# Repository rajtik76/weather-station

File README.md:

# Balcony Station

A weather station on an east-facing balcony in Plzeň, Czech Republic,
measuring temperature, humidity and pressure. Its goal is to estimate
outdoor air temperature as accurately as possible by correcting the
heating error of this particular radiation shield and balcony setup.

The SHT4x measures temperature inside a passive radiation shield. Sunlight
can heat the shield and make the sensor read above the surrounding air
temperature. The project aims to retain the original readings and show a
corrected estimate alongside them.

**Current status:** a PHP correction model can be calibrated and evaluated
against ČHMÚ observations through Artisan. Overview and Charts display
the original temperature alongside the calculated shade estimate. The
Reference page compares the shade estimate with the shade reference and
Mikulka by day, up to 30 days back, and reports deviations over the last
30 days.

Running at [weather.rajtik.com](https://weather.rajtik.com).

## Reference and evaluation

ČHMÚ Plzeň-Mikulka, approximately 3.5 km away, is the professional reference
for developing and evaluating the correction. Its historical observations
are available through [ČHMÚ open data](https://opendata.chmi.cz/meteorology/climate/).
Location, elevation and microclimate can produce real differences between
Mikulka and the balcony; agreement with Mikulka is a measurable reference,
with that limitation.

The correction is therefore fitted and judged against a shade reference
(`ShadeReference`): Mikulka shifted by the balcony's own offset from it.
The offset is read while the shield is in shade, in the hour before the
sun reaches it (below 300 lx) and 30 to 60 minutes after the sun has left,
and runs in a straight line between the two from the moment the sun
reaches the shield until an hour after it leaves, while the shield's
heating history decays. Outside that window the shade reference is
Mikulka. A day without both anchors has no reference in that window, and
its readings there are left out of calibration and validation. On overcast mornings between 1 October
and 5 November 2026, when the right difference is zero, the shade reference
was 0.21 °C from zero on average and Mikulka 0.52 °C. The straight line
between the anchors is an assumption that overcast mornings cannot check.

The correction will be evaluated against the uncorrected sensor on the
same observations, using days excluded from calibration. Both the mean
absolute error and the mean signed error should be compared, with sunny
periods and nights evaluated separately.

The setup changed during the record:

- Radiation shield installed on **16 September 2026 at 15:00 Europe/Prague**
- BME280 replaced by an SHT4x on 23 September 2026
- SHT4x sensor replaced and VEML7700 installed on 30 September 2026

These events are recorded in `station_events` and marked on the charts.
They do not block calibration or invalidate an existing correction model.

## Temperature correction

The model estimates solar heating from light inside the shield and the
Sun's position relative to the balcony wall. Feature version 2 combines
the current light with exponentially weighted histories of 10 and 30
minutes, and scales the 10 minute history by low sun (below 20° elevation
the shield heats more for the same light) and by the microphone's 25 Hz
band (wind ventilates the shield). Regularized regression learns the
response of this installation; heating coefficients stay non-negative, the
wind term takes either sign. Version 1 (light with 20 and 60 minute histories)
is still applied for calibrations trained with it. The shade estimate is
the measured temperature minus the estimated heating; original records
are unchanged.

Calibration and inference run in PHP, without a separate service. ČHMÚ
temperature is used for calibration and evaluation only. The running model
uses the station's light and sound history, time and calibrated
installation geometry.
The wall direction is the balcony facade at 71.8° clockwise from true north;
override it when calibrating another installation.

```sh
php artisan temperature:import-reference
php artisan temperature:import-reference --days=30
php artisan temperature:import-reference --month=2026-09
php artisan temperature:import-reference /path/to/mikulka-20261001.json
php artisan temperature:calibrate sensor-001 --from=2026-09-30 --validate-from=2026-10-10 --until=2026-10-15
php artisan temperature:show sensor-001
```

Dates are local calendar boundaries in Europe/Prague, with exclusive ends.
Station events do not restrict the calibration range. At least
seven calibration days and three later validation days must each have
100 reference pairs; calibration also needs two sunlit mornings. Validation
reports MAE and signed error for the same raw and corrected observations,
split into sun-facing periods, daytime shade and night, plus each day.
The validation days are never used to fit coefficients. An accepted model
is available to inference only after its validation period ends.

The scheduler imports the previous and current UTC day's references every
hour. Run `--days=30` once to backfill history from monthly and daily
archives; the scheduled import continues to fetch only yesterday and today. Missing reference periods stay missing. ČHMÚ's good
and unknown-quality observations are eligible; suspect, poor, estimated,
missing and flagged observations are excluded.

The model needs an uninterrupted hour of light measurements after startup
or a gap. Unsupported readings and inputs beyond its calibrated light or
heating range return no estimate. Validation scores against the shade
reference. With at least two sunlit validation mornings, acceptance
requires a sun-facing MAE at least 10% below the raw sensor and a smaller
sun-facing bias; with fewer, the sun-facing MAE may not exceed the raw
sensor's by more than 0.05 °C. Always: no overall MAE increase above
0.05 °C, at least 90% validation coverage, no MAE increase above 0.05 °C at
night or 0.1 °C in daytime shade. A retrained model must also be within
0.02 °C of the model in use, overall and sun-facing, on the same pairs.

The model corrects solar heating. Local air differences, reflected heat
from the building and night-time radiation are not corrected: in afternoon
shade the balcony runs up to about a degree colder than Mikulka on sunny,
calm days and warmer on windy, overcast ones, and that is the balcony's
air, not the shield. A smaller error against the shade reference is
evidence of a better shield correction, not a measurement of the remaining
error on the balcony. Calibration over a few autumn days
does not establish accuracy in other seasons.

## Measurements

```text
SHT4x    --I2C--+
VEML7700 --I2C--+
BMP280   --I2C--+--> ESP32 --HTTPS--> Laravel API --> PostgreSQL
INMP441  --I2S--+                                      |
                                                 Livewire pages
```

- SHT4x: temperature and humidity, outside in the radiation shield
- BMP280: pressure, on the indoor base board; its temperature is unused
- VEML7700: light inside the shield, retained as a potential correction input
- INMP441: sound in the shield, with an experimental indication of rain from its spectrum
- Samples every 30 seconds, uploaded as ten-minute windows with means and extremes
- Original measurements remain stored in the firmware's units; display conversions happen on read

Light behind the shield's louvers is specific to this mounting. Its absolute
lux values are not an open-sky radiation measurement. The microphone's rain
indication is experimental: its thresholds were fitted to this mounting
against ČHMÚ Mikulka's rain gauge, and the owner's reports on Discord keep
checking it.

## Run it

Requires PHP 8.4, Node 24 and Docker. Docker Compose runs PostgreSQL 18;
Laravel Herd serves the local site and Vite provides the development assets.

```sh
docker compose up -d
composer setup
npm run dev
```

For a local demonstration, `php artisan migrate:fresh --seed` replaces the
local database with a month of sample measurements for two stations. The
sample weather series comes from ČHMÚ Plzeň-Mikulka, with synthetic station
variation, light and sound added for the dashboard.

ČHMÚ data is licensed CC BY 4.0. Source: Czech Hydrometeorological Institute.
The sample series uses hourly means of its ten-minute observations for
August 2025. Sample pressure is adjusted from Mikulka's elevation of 359.8 m
to the balcony's 345 m before the synthetic station variation is added.

## Documentation

- [`docs/development.md`](docs/development.md): application structure, configuration, checks and deployment
- [`docs/api.md`](docs/api.md): ingest protocol and storage
- [`firmware/README.md`](firmware/README.md): wiring, protocol and hardware notes
- [`firmware/CHANGELOG.md`](firmware/CHANGELOG.md): firmware history
- `docs/hardware/kicad/`: station, shield hub and base board KiCad projects

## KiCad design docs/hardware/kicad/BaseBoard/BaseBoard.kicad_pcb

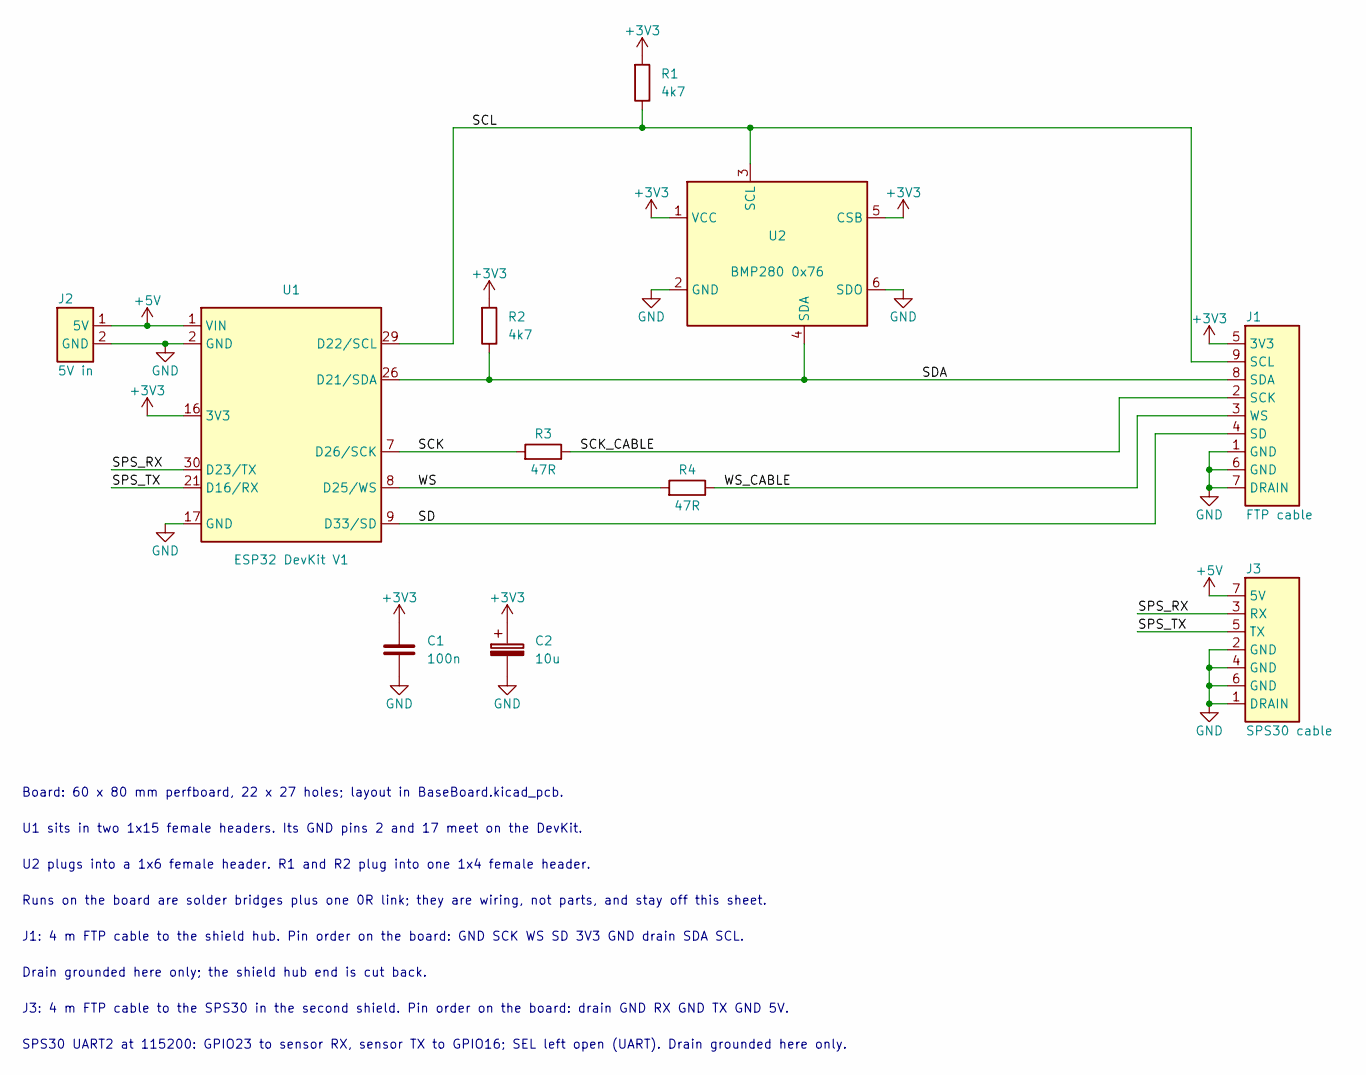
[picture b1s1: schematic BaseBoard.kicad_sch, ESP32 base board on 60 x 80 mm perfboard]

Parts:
C1: 100n; C_Disc_P2.54
C2: 10u; CP_Radial_D5.0mm_P2.54
J1: FTP cable; PinHeader_1x09
J2: 5V in; PinHeader_1x02
J3: SPS30 cable; PinHeader_1x07
R1, R2: 4k7; R_Socketed_1x02
R3, R4: 47R; R_Axial_P10.16
U1: ESP32 DevKit V1; DOIT_ESP32_DevKit_V1_Socketed
U2: BMP280 0x76; BMP280_Module_Socketed

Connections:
+3V3: C1.1, C2.1 (+), J1.5 (3V3), R1.1, R2.1, U1.16 (3V3), U2.1 (VCC), U2.5 (CSB); also elsewhere on the board
+5V: J2.1 (5V), J3.7 (5V), U1.1 (VIN)
/SCK: R3.1, U1.7 (D26/SCK)
/SCK_CABLE: J1.2 (SCK), R3.2
/SCL: J1.9 (SCL), R1.2, U1.29 (D22/SCL), U2.3 (SCL)
/SD: J1.4 (SD), U1.9 (D33/SD)
/SDA: J1.8 (SDA), R2.2, U1.26 (D21/SDA), U2.4 (SDA)
/SPS_RX: J3.3 (RX), U1.30 (D23/TX)
/SPS_TX: J3.5 (TX), U1.21 (D16/RX)
/WS: R4.1, U1.8 (D25/WS)
/WS_CABLE: J1.3 (WS), R4.2
GND: C1.2, C2.2 (-), J1.1 (GND), J1.6 (GND), J1.7 (DRAIN), J2.2 (GND), J3.1 (DRAIN), J3.2 (GND), J3.4 (GND), J3.6 (GND), U1.2 (GND), U1.17 (GND), U2.2 (GND), U2.6 (SDO)

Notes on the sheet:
Board: 60 x 80 mm perfboard, 22 x 27 holes; layout in BaseBoard.kicad_pcb.
U1 sits in two 1x15 female headers. Its GND pins 2 and 17 meet on the DevKit.
U2 plugs into a 1x6 female header. R1 and R2 plug into one 1x4 female header.
Runs on the board are solder bridges plus one 0R link; they are wiring, not parts, and stay off this sheet.
J1: 4 m FTP cable to the shield hub. Pin order on the board: GND SCK WS SD 3V3 GND drain SDA SCL.
Drain grounded here only; the shield hub end is cut back.
J3: 4 m FTP cable to the SPS30 in the second shield. Pin order on the board: drain GND RX GND TX GND 5V.
SPS30 UART2 at 115200: GPIO23 to sensor RX, sensor TX to GPIO16; SEL left open (UART). Drain grounded here only.

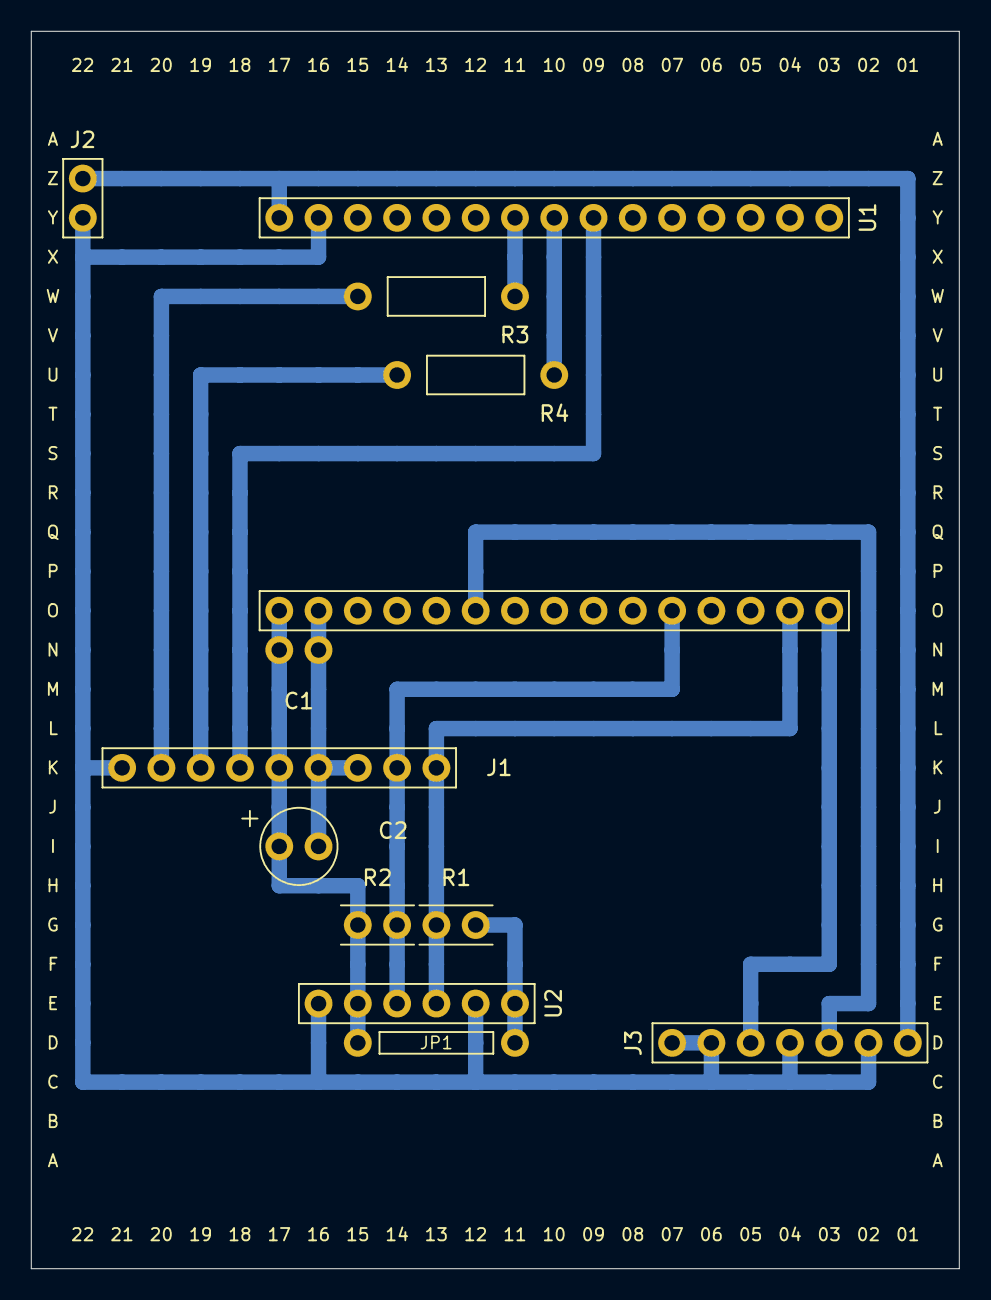
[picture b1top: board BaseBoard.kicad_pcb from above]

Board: 2 copper layers, 60.0 x 80.0 mm, 13 parts (0 on the bottom side), 12 nets.

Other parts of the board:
JP1: 0R; R_Jumper_P10.16
PERF1: perfboard 22 x 27; Perfboard_22x27

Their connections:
+3V3: JP1.1, JP1.2; also elsewhere on the board

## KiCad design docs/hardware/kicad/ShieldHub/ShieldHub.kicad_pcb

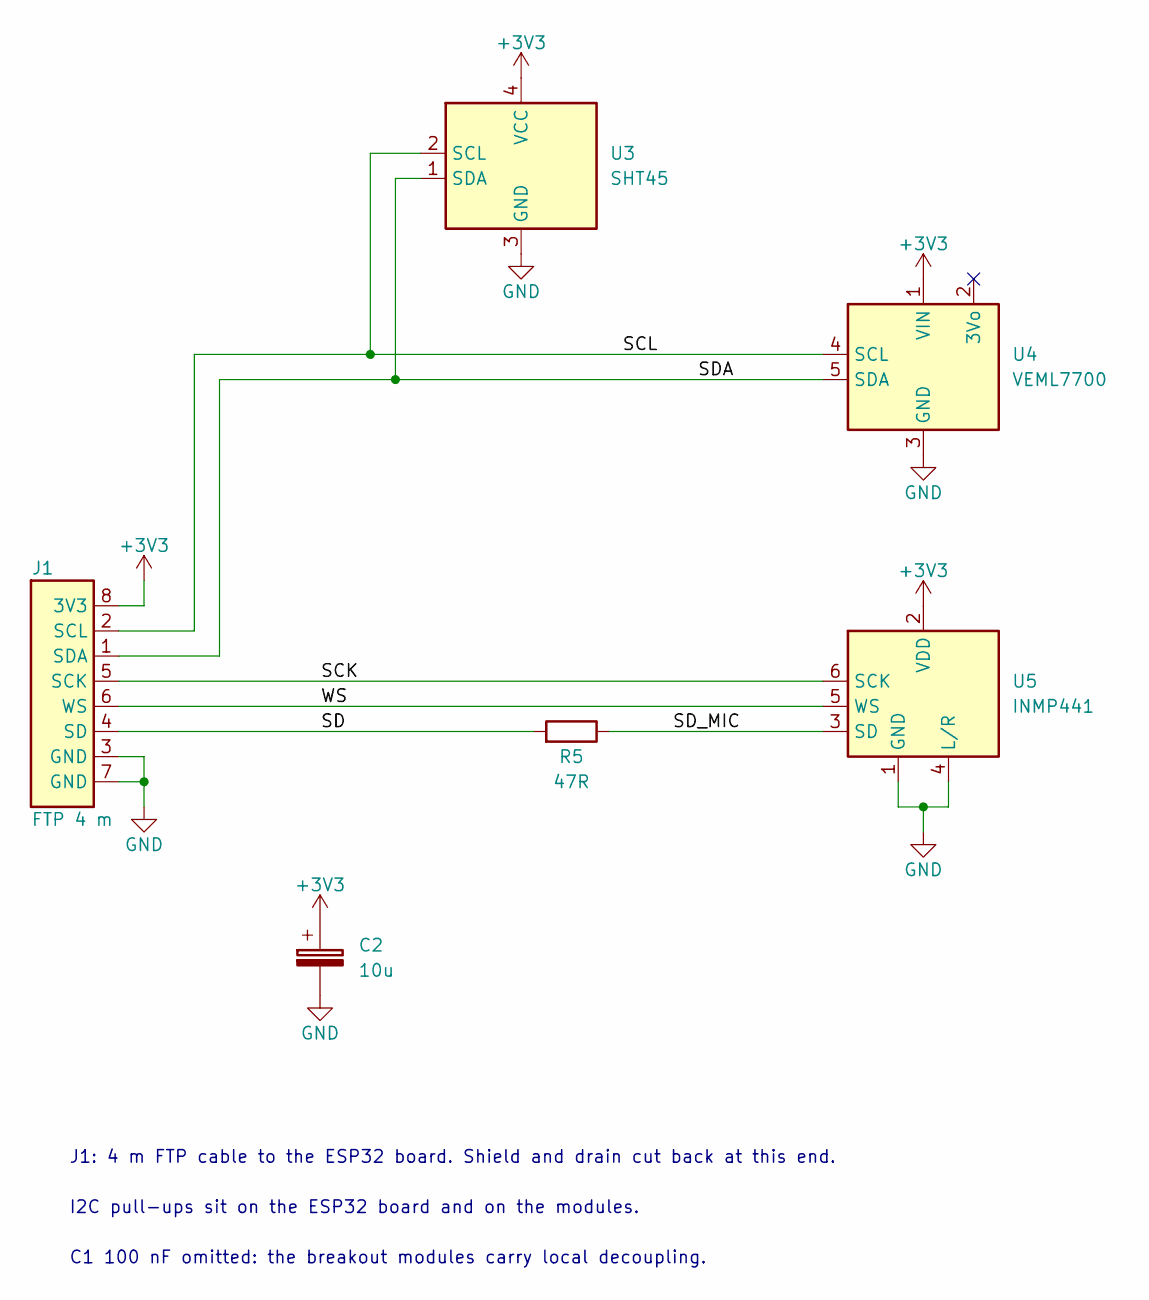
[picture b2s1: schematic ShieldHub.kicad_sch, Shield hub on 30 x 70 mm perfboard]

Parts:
C2: 10u; C_Radial_P2_54
J1: FTP 4 m; FTP_8_Wires
R5: 47R; R_Axial_P9_16
U3: SHT45; SHT45_LaskaKit
U4: VEML7700; VEML7700_Techfun
U5: INMP441; INMP441_Round

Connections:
+3V3: C2.1 (+), J1.8 (3V3), U3.4 (VCC), U4.1 (VIN), U5.2 (VDD)
/SCK: J1.5 (SCK), U5.6 (SCK)
/SCL: J1.2 (SCL), U3.2 (SCL), U4.4 (SCL)
/SD: J1.4 (SD), R5.1
/SDA: J1.1 (SDA), U3.1 (SDA), U4.5 (SDA)
/SD_MIC: R5.2, U5.3 (SD)
/WS: J1.6 (WS), U5.5 (WS)
GND: C2.2 (-), J1.3 (GND), J1.7 (GND), U3.3 (GND), U4.3 (GND), U5.1 (GND), U5.4 (L/R)

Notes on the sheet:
J1: 4 m FTP cable to the ESP32 board. Shield and drain cut back at this end.
I2C pull-ups sit on the ESP32 board and on the modules.
C1 100 nF omitted: the breakout modules carry local decoupling.

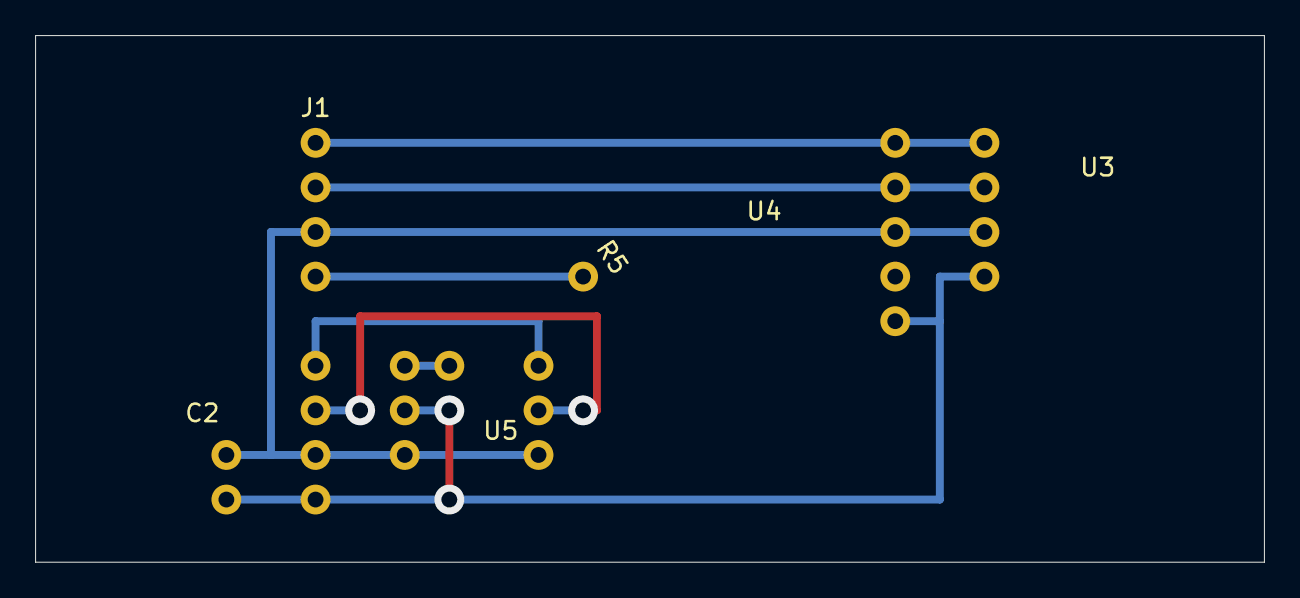
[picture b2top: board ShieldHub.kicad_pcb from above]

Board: 2 copper layers, 70.0 x 30.0 mm, 6 parts (0 on the bottom side), 8 nets.

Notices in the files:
README.md:
License: MIT
